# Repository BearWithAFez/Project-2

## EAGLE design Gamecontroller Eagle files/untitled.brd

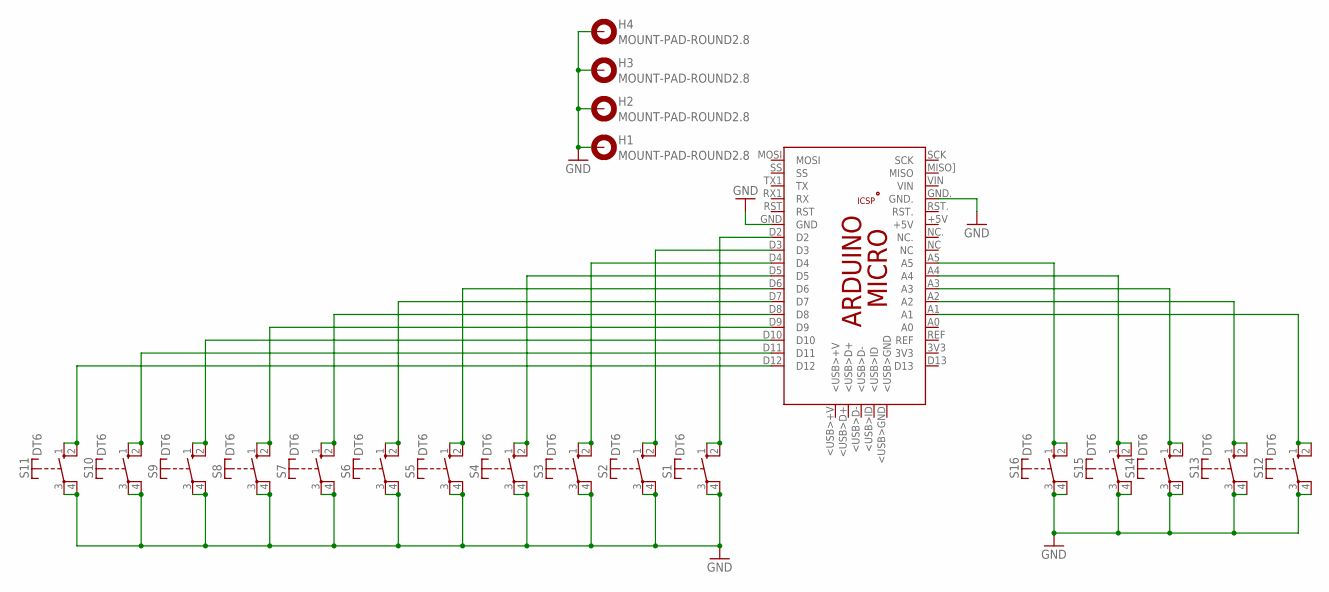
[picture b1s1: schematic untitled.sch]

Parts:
H1, H2, H3, H4: MOUNT-PAD-ROUND2.8; 2,8-PAD
PCB2: ARDUINO_MICRO
S1, S2, S3, S4, S5, S6, S7, S8, S9, S10, S11, S12, S13, S14, S15, S16: DT6

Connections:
GND: H1.B2,8, H2.B2,8, H3.B2,8, H4.B2,8, PCB2.GND, PCB2.GND., S1.3, S1.4, S2.3, S2.4, S3.3, S3.4, S4.3, S4.4, S5.3, S5.4, S6.3, S6.4, S7.3, S7.4, S8.3, S8.4, S9.3, S9.4, S10.3, S10.4, S11.3, S11.4, S12.3, S12.4, S13.3, S13.4, S14.3, S14.4, S15.3, S15.4, S16.3, S16.4
unnamed: PCB2.D2, S1.1 (S), S1.2 (S)
unnamed: PCB2.D3, S2.1 (S), S2.2 (S)
unnamed: PCB2.D4, S3.1 (S), S3.2 (S)
unnamed: PCB2.D5, S4.1 (S), S4.2 (S)
unnamed: PCB2.D6, S5.1 (S), S5.2 (S)
unnamed: PCB2.D7, S6.1 (S), S6.2 (S)
unnamed: PCB2.D8, S7.1 (S), S7.2 (S)
unnamed: PCB2.D9, S8.1 (S), S8.2 (S)
unnamed: PCB2.D10, S9.1 (S), S9.2 (S)
unnamed: PCB2.D11, S10.1 (S), S10.2 (S)
unnamed: PCB2.D12, S11.1 (S), S11.2 (S)
unnamed: PCB2.A5, S16.1 (S), S16.2 (S)
unnamed: PCB2.A4, S15.1 (S), S15.2 (S)
unnamed: PCB2.A3, S14.1 (S), S14.2 (S)
unnamed: PCB2.A2, S13.1 (S), S13.2 (S)
unnamed: PCB2.A1, S12.1 (S), S12.2 (S)

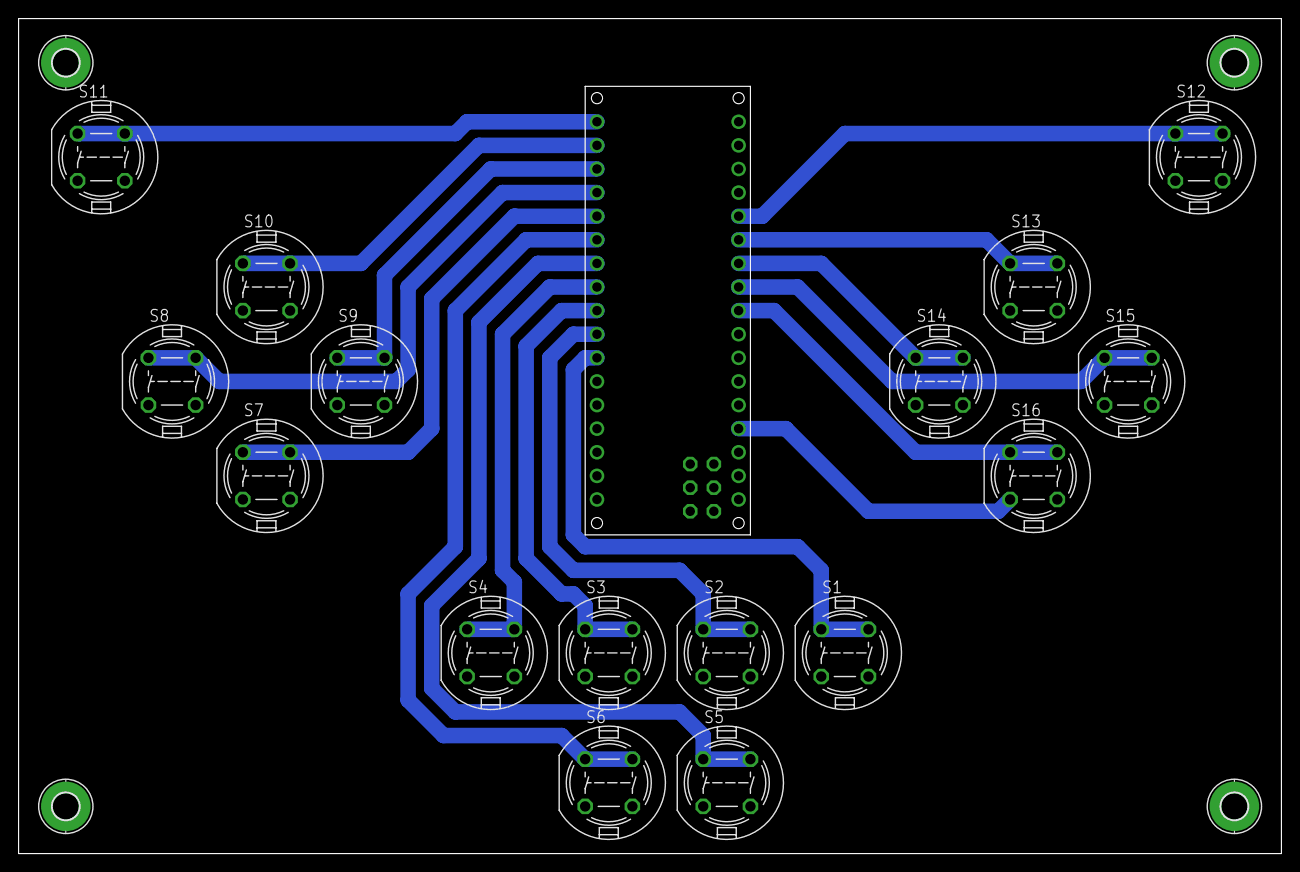
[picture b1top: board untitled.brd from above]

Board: 2 copper layers, 135.9 x 89.8 mm, 21 parts (1 on the bottom side), 17 nets.

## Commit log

2018-02-21 Upload from GITLAB
